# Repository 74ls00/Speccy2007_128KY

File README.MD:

# Speccy 2007 128K AY PAL SCART 2017

За основу взята единственная на тот момент полная схема 128к от Ljubitel, архив его проекта тут https://github.com/74ls00/Speccy2007_by_Ljubitel

Добавлен кодер PAL и разъём SCART.

Проект в процессе тестирования

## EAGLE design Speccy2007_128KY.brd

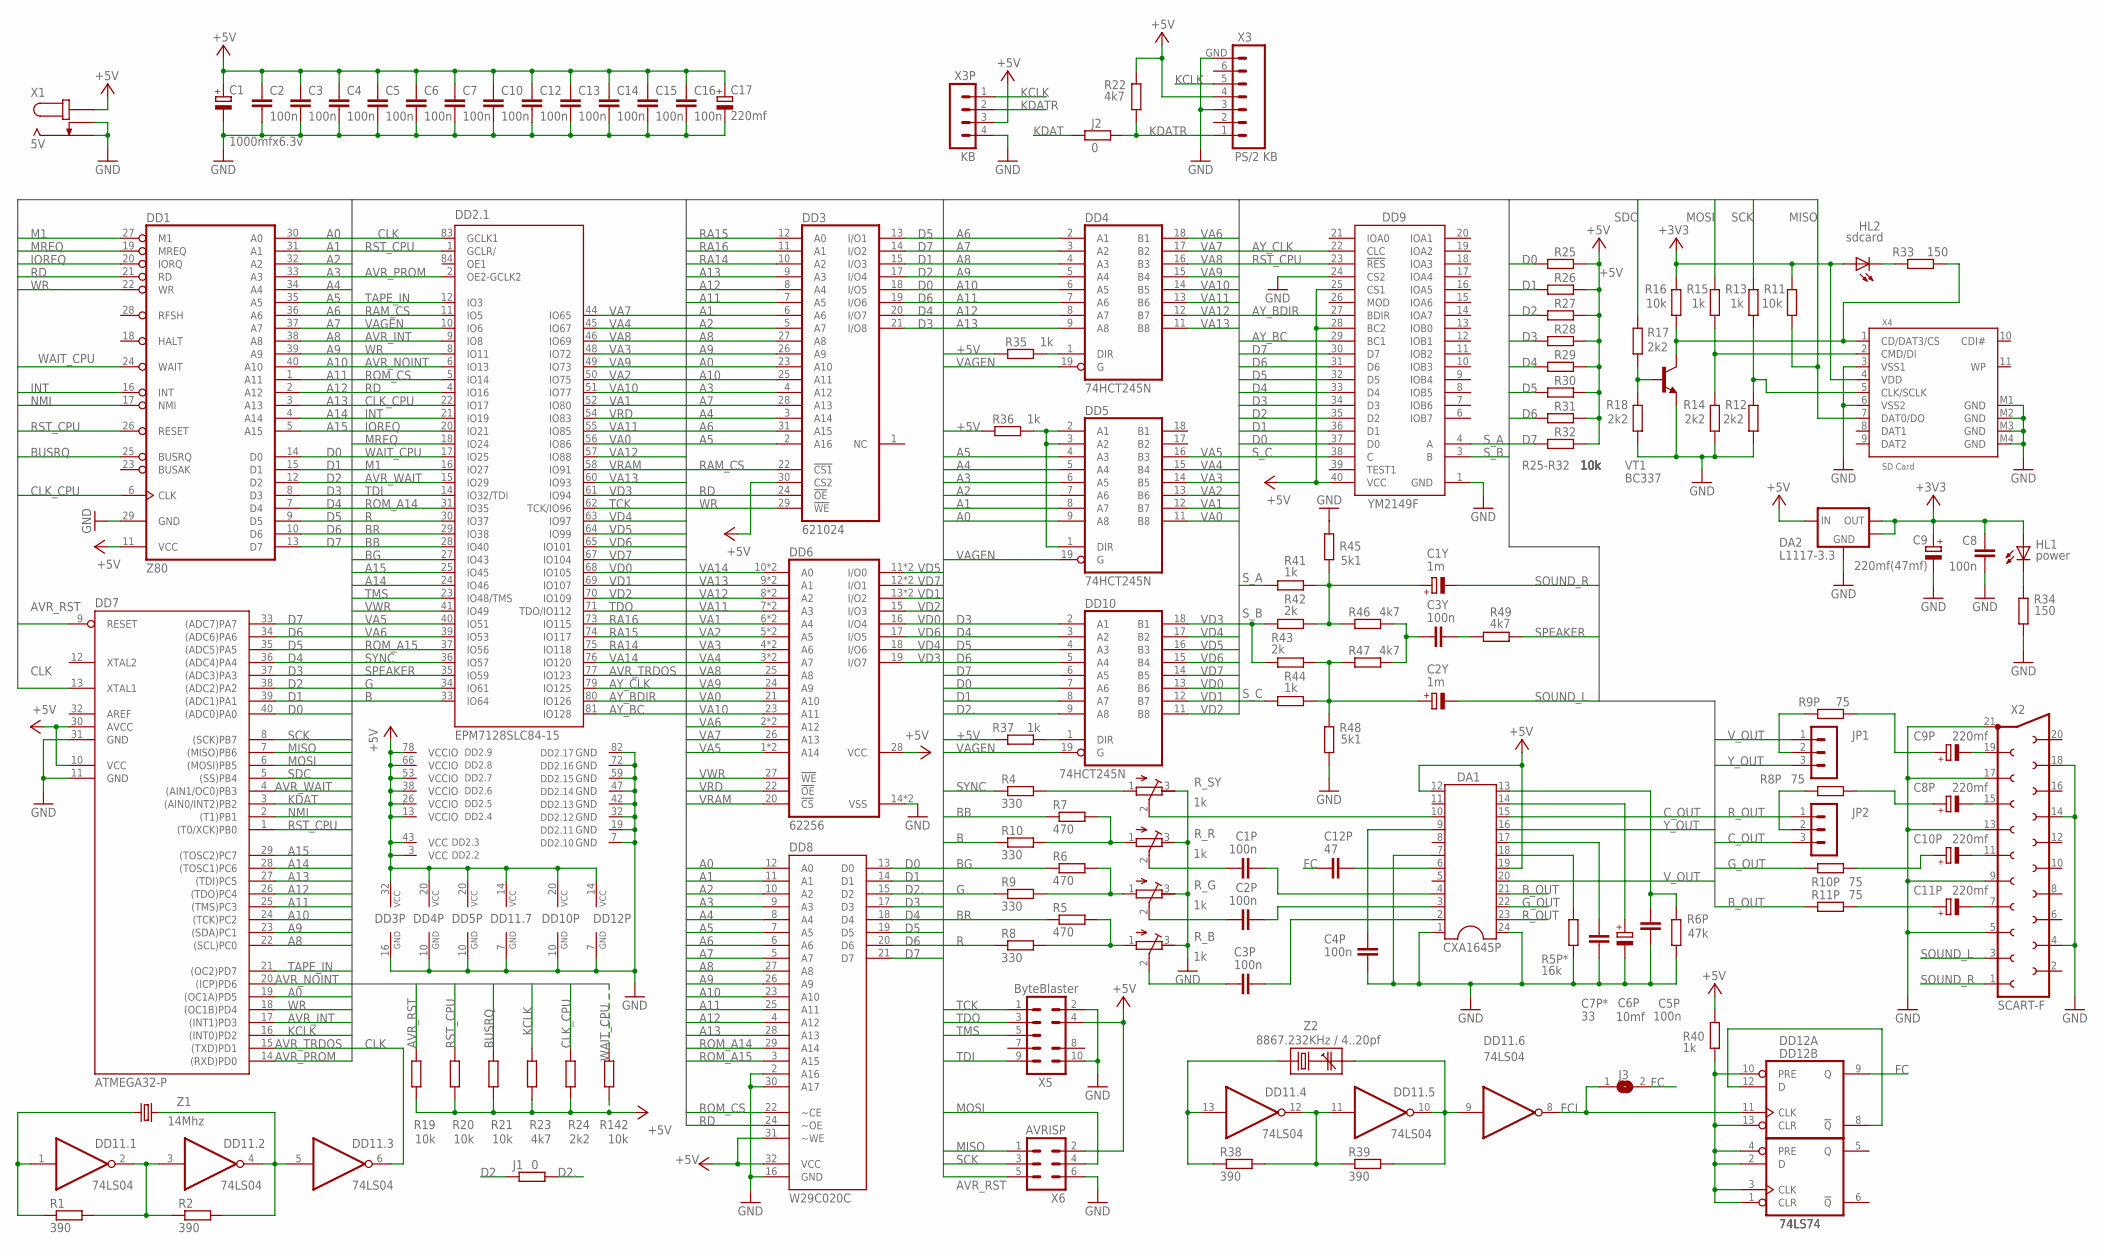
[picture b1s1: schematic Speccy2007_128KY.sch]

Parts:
C1: 1000mfx6.3v; E3,5-8
C1P, C2, C2P, C3, C3P, C3Y, C4P, C5, C7, C8, C10, C12, C13, C14, C15, C16: 100n; C0805
C1Y, C2Y: 1m; E2,5-5
C4, C5P, C6: 100n; C1206
C6P: 10mf; E2,5-5
C7P*: 33; C1206
C8P, C9P, C10P, C11P, C17: 220mf; E2,5-6
C9: 220mf(47mf); E2,5-6
C12P: 47; C0805
DA1: CXA1645P; DIL24-4
DA2: L1117-3.3; SOT-223
DD1: Z80; DIL40
DD2: EPM7128SLC84-15; PGA-84-B
DD3: 621024; DIL32
DD4, DD5, DD10: 74HCT245N; DIL20
DD6: 62256; DIL28+6
DD7: ATMEGA32-P; DIL40
DD8: W29C020C; DIL32
DD9: YM2149F; DIL40
DD11: 74LS04; DIL14
DD12: 74LS74; DIL14O
HL1: power; SML0805
HL2: sdcard; SML0805
J1: 0; M1206
J2: 0; R1206
J3: SJ
JP1, JP2: MA03-1
R1, R2, R38, R39: 390; R0805
R4, R8, R9, R10: 330; R0805
R5: 470; R0805
R5P*: 16k; M1206
R6: 470; R1206
R6P: 47k; R0805
R7: 470; 0207/10
R8P, R9P, R10P, R11P: 75; R1206
R11, R16, R20, R25, R27, R28, R29, R30, R31, R32: 10k; R0805
R12: 2k2; R1206
R13, R15, R35, R36, R37, R40, R41: 1k; R0805
R14, R17, R18: 2k2; R0805
R19, R26: 10k; M0805
R21, R142: 10k; 0207/10
R22, R47, R49: 4k7; R0805
R23, R46: 4k7; R1206
R24: 2k2; 0207/10
R33: 150; R1206
R34: 150; R0805
R42, R43: 2k; R0805
R44: 1k; R1206
R45: 5k1; R1206
R48: 5k1; R0805
R_B: 1k; RTRIM3296W
R_G: 1k; RTRIM3296W
R_R: 1k; RTRIM3296W
R_SY: 1k; RTRIM3296W
VT1: BC337; TO92-CBE
X1: 5V; POWER3.5
X2: SCART-F
X3: PS/2 KB; MINI-DIN6
X3P: KB; MA04-1
X4: SD Card; SDCMF-10915W010
X5: ByteBlaster; MA05-2
X6: AVRISP; MA03-2
Z1: 14Mhz; HC49U-H
Z2: 8867.232KHz / 4..20pf; HC49U-H

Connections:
+3V3: C8.1, C9.+, DA2.2 (OUT), DA2.4 (OUT'), HL1.A, HL2.A, R11.2, R16.2, X4.4 (VDD)
+5V: C1.+, C2.1, C3.1, C4.1, C5.1, C6.1, C7.1, C10.1, C12.1, C13.1, C14.1, C15.1, C16.1, C17.+, DA1.12, DA1.19, DA2.3 (IN), DD1.11 (VCC), DD2.3 (VCC), DD2.13 (VCCIO), DD2.26 (VCCIO), DD2.38 (VCCIO), DD2.43 (VCC), DD2.53 (VCCIO), DD2.66 (VCCIO), DD2.78 (VCCIO), DD3.30 (CS2), DD3.32 (VCC), DD4.20 (VCC), DD5.20 (VCC), DD6.28 (VCC), DD7.10 (VCC), DD7.30 (AVCC), DD8.31 (~WE), DD8.32 (VCC), DD9.25 (CS1), DD9.28 (BC2), DD9.40 (VCC), DD10.20 (VCC), DD11.14 (VCC), DD12.14 (VCC), R19.1, R20.1, R21.1, R22.2, R23.1, R24.1, R25.2, R26.2, R27.2, R28.2, R29.2, R30.2, R31.2, R32.2, R35.2, R36.2, R37.2, R40.2, R142.1, X1.P$1 (1), X3.4, X3P.3, X5.4, X6.2
A0: DD1.30 (A0), DD3.23 (A10), DD5.9 (A8), DD7.19 ((OC1A)PD5), DD8.12 (A0)
A1: DD1.31 (A1), DD3.6 (A6), DD5.8 (A7), DD8.11 (A1)
A2: DD1.32 (A2), DD3.5 (A7), DD5.7 (A6), DD8.10 (A2)
A3: DD1.33 (A3), DD3.4 (A12), DD5.6 (A5), DD8.9 (A3)
A4: DD1.34 (A4), DD3.3 (A14), DD5.5 (A4), DD8.8 (A4)
A5: DD1.35 (A5), DD3.2 (A16), DD5.4 (A3), DD8.7 (A5)
A6: DD1.36 (A6), DD3.31 (A15), DD4.2 (A1), DD8.6 (A6)
A7: DD1.37 (A7), DD3.28 (A13), DD4.3 (A2), DD8.5 (A7)
A8: DD1.38 (A8), DD3.27 (A8), DD4.4 (A3), DD7.22 ((SCL)PC0), DD8.27 (A8)
A9: DD1.39 (A9), DD3.26 (A9), DD4.5 (A4), DD7.23 ((SDA)PC1), DD8.26 (A9)
A10: DD1.40 (A10), DD3.25 (A11), DD4.6 (A5), DD7.24 ((TCK)PC2), DD8.23 (A10)
A11: DD1.1 (A11), DD3.7 (A5), DD4.7 (A6), DD7.25 ((TMS)PC3), DD8.25 (A11)
A12: DD1.2 (A12), DD3.8 (A4), DD4.8 (A7), DD7.26 ((TDO)PC4), DD8.4 (A12)
A13: DD1.3 (A13), DD3.9 (A3), DD4.9 (A8), DD7.27 ((TDI)PC5), DD8.28 (A13)
A14: DD1.4 (A14), DD2.24 (IO46), DD7.28 ((TOSC1)PC6)
A15: DD1.5 (A15), DD2.25 (IO45), DD7.29 ((TOSC2)PC7)
AVR_INT: DD2.9 (IO8), DD7.17 ((INT1)PD3)
AVR_NOINT: DD2.6 (IO13), DD7.20 ((ICP)PD6)
AVR_PROM: DD2.2 (OE2-GCLK2), DD7.14 ((RXD)PD0)
AVR_RST: DD7.9 (RESET), R19.2, X6.5
AVR_TRDOS: DD2.77 (IO123), DD7.15 ((TXD)PD1)
AVR_WAIT: DD2.15 (IO29), DD7.4 ((AIN1/OC0)PB3)
AY_BC: DD2.81 (IO128), DD9.29 (BC1)
AY_BDIR: DD2.80 (IO126), DD9.27 (BDIR)
AY_CLK: DD2.79 (IO125), DD9.22 (CLC)
B: DD2.33 (IO64), R10.1
BB: DD2.28 (IO40), R7.1
BG: DD2.27 (IO43), R6.1
BR: DD2.29 (IO38), R5.1
BUSRQ: DD1.25 (BUSRQ), R21.2
B_OUT: DA1.21, R11P.1
CDDAT3: R16.1, R33.1, VT1.C, X4.1 (CD/DAT3/CS)
CLK: DD2.83 (GCLK1), DD7.13 (XTAL1), DD11.6 (O)
CLK_CPU: DD1.6 (CLK), DD2.22 (IO17), R24.2
C_OUT: DA1.15, JP2.3
D0: DD1.14 (D0), DD3.18 (I/O5), DD7.40 ((ADC0)PA0), DD8.13 (D0), DD9.37 (D0), DD10.7 (A6), R25.1
D1: DD1.15 (D1), DD3.15 (I/O3), DD7.39 ((ADC1)PA1), DD8.14 (D1), DD9.36 (D1), DD10.8 (A7), R26.1
D2: DD1.12 (D2), DD7.38 ((ADC2)PA2), DD9.35 (D2), J1.1, R27.1
D2.: DD3.17 (I/O4), DD8.15 (D2), DD10.9 (A8), J1.2
D3: DD1.8 (D3), DD3.21 (I/O8), DD7.37 ((ADC3)PA3), DD8.17 (D3), DD9.34 (D3), DD10.2 (A1), R28.1
D4: DD1.7 (D4), DD3.20 (I/O7), DD7.36 ((ADC4)PA4), DD8.18 (D4), DD9.33 (D4), DD10.3 (A2), R29.1
D5: DD1.9 (D5), DD3.13 (I/O1), DD7.35 ((ADC5)PA5), DD8.19 (D5), DD9.32 (D5), DD10.4 (A3), R30.1
D6: DD1.10 (D6), DD3.19 (I/O6), DD7.34 ((ADC6)PA6), DD8.20 (D6), DD9.31 (D6), DD10.5 (A4), R31.1
D7: DD1.13 (D7), DD3.14 (I/O2), DD7.33 ((ADC7)PA7), DD8.21 (D7), DD9.30 (D7), DD10.6 (A5), R32.1
FC: C12P.1, DD12.9 (Q), J3.2
FCI: DD11.8 (O), DD12.11 (CLK), J3.1
G: DD2.34 (IO61), R9.1
GND: C1.-, C2.2, C3.2, C4.2, C4P.1, C5.2, C5P.1, C6.2, C6P.-, C7.2, C7P*.2, C8.2, C9.-, C10.2, C12.2, C13.2, C14.2, C15.2, C16.2, C17.-, DA1.1, DA1.7, DA1.24, DA2.1 (GND), DD1.29 (GND), DD2.7 (GND), DD2.19 (GND), DD2.32 (GND), DD2.42 (GND), DD2.47 (GND), DD2.59 (GND), DD2.72 (GND), DD2.82 (GND), DD3.16 (GND), DD4.10 (GND), DD5.10 (GND), DD6.14 (VSS), DD6.P$14 (VSS), DD7.11 (GND), DD7.31 (GND), DD8.2 (A16), DD8.16 (GND), DD8.30 (A17), DD9.1 (GND), DD9.24 (CS2), DD10.10 (GND), DD11.7 (GND), DD12.7 (GND), R5P*.1, R6P.1, R12.1, R14.1, R18.1, R34.1, R45.2, R48.2, R_B.3 (A), R_G.3 (A), R_R.3 (A), R_SY.3 (A), VT1.E, X1.P$2 (2), X1.P$3 (3), X2.4, X2.5, X2.9, X2.13, X2.14, X2.17, X2.18, X2.21, X3.3, X3.GND (7), X3P.4, X4.3 (VSS1), X4.6 (VSS2), X4.M1 (GND), X4.M2 (GND), X4.M3 (GND), X4.M4 (GND), X5.2, X5.10, X6.6
G_OUT: DA1.22, R10P.1
INT: DD1.16 (INT), DD2.21 (IO19)
IOREQ: DD1.20 (IORQ), DD2.20 (IO21)
KCLK: DD7.16 ((INT0)PD2), R23.2, X3.5, X3P.1
KDAT: DD7.3 ((AIN0/INT2)PB2), J2.1
KDATR: J2.2, R22.1, X3.1, X3P.2
M1: DD1.27 (M1), DD2.16 (IO27)
MISO: DD7.7 ((MISO)PB6), R11.1, X4.7 (DAT0/DO), X6.1
MOSI: DD7.6 ((MOSI)PB5), R15.2, X6.4
MREQ: DD1.19 (MREQ), DD2.18 (IO24)
unnamed: DD11.4 (O), DD11.5 (I), R2.2, Z1.2
unnamed: C3Y.1, R46.2, R47.2
unnamed: C3Y.2, R49.1
unnamed: C1Y.+, R41.2, R42.2, R45.1, R46.1
unnamed: DD11.2 (O), DD11.3 (I), R1.2, R2.1
unnamed: R4.2, R_SY.1 (E)
unnamed: C2Y.+, R43.2, R44.2, R47.1, R48.1
unnamed: R7.2, R10.2, R_R.1 (E)
unnamed: R6.2, R9.2, R_G.1 (E)
unnamed: R5.2, R8.2, R_B.1 (E)
unnamed: C1P.1, R_R.2 (S)
unnamed: DD11.1 (I), R1.1, Z1.1
unnamed: C2P.1, R_G.2 (S)
unnamed: C3P.1, R_B.2 (S)
unnamed: R17.1, R18.2, VT1.B
unnamed: R12.2, R13.1, X4.5 (CLK/SCLK)
unnamed: R14.2, R15.1, X4.2 (CMD/DI)
unnamed: DA1.10, R_SY.2 (S)
unnamed: DD10.1 (DIR), R37.1
unnamed: DD5.1 (DIR), DD5.2 (A1), DD5.3 (A2), R36.1
unnamed: C9P.-, X2.19
unnamed: JP1.2, R9P.1
unnamed: C4P.2, DA1.9
unnamed: C8P.-, X2.15
unnamed: JP2.2, R8P.1
unnamed: C10P.-, X2.11
unnamed: C11P.-, X2.7
unnamed: C10P.+, R10P.2
unnamed: C3P.2, DA1.2
unnamed: C11P.+, R11P.2
unnamed: DD12.8 (!Q), DD12.12 (D)
unnamed: HL1.C, R34.2
unnamed: DD12.1 (CLR), DD12.2 (D), DD12.3 (CLK), DD12.4 (PRE), DD12.10 (PRE), DD12.13 (CLR), R40.1
unnamed: HL2.C, R33.2
unnamed: DD4.1 (DIR), R35.1
unnamed: DD11.11 (I), DD11.12 (O), R38.2, R39.1
unnamed: DD11.9 (I), DD11.10 (O), R39.2, Z2.2
unnamed: DD11.13 (I), R38.1, Z2.1
unnamed: C2P.2, DA1.3
unnamed: C1P.2, DA1.4
unnamed: C9P.+, R9P.2
unnamed: DA1.18, R5P*.2
unnamed: C5P.2, DA1.13, R6P.2
unnamed: C6P.+, DA1.14
unnamed: C8P.+, R8P.2
unnamed: C12P.2, DA1.6
unnamed: C7P*.1, DA1.17
NMI: DD1.17 (NMI), DD7.2 ((T1)PB1)
R: DD2.30 (IO37), R8.1
RA14: DD2.75 (IO118), DD3.10 (A2)
RA15: DD2.74 (IO117), DD3.12 (A0)
RA16: DD2.73 (IO115), DD3.11 (A1)
RAM_CS: DD2.11 (IO5), DD3.22 (!CS1)
RD: DD1.21 (RD), DD2.4 (IO16), DD3.24 (!OE), DD8.24 (~OE)
ROM_A14: DD2.31 (IO35), DD8.29 (A14)
ROM_A15: DD2.37 (IO56), DD8.3 (A15)
ROM_CS: DD2.5 (IO14), DD8.22 (~CE)
RST_CPU: DD1.26 (RESET), DD2.1 (GCLR/), DD7.1 ((T0/XCK)PB0), DD9.23 (!RES), R20.2
R_OUT: DA1.23, JP2.1
SCK: DD7.8 ((SCK)PB7), R13.2, X6.3
SDC: DD7.5 ((SS)PB4), R17.2
SOUND_L: C2Y.-, X2.3
SOUND_R: C1Y.-, X2.1
SPEAKER: DD2.35 (IO59), R49.2
SYNC: DD2.36 (IO57), R4.1
S_A: DD9.4 (A), R41.1
S_B: DD9.3 (B), R42.1, R43.1
S_C: DD9.38 (C), R44.1
TAPE_IN: DD2.12 (IO3), DD7.21 ((OC2)PD7)
TCK: DD2.62 (TCK/IO96), X5.1
TDI: DD2.14 (IO32/TDI), X5.9
TDO: DD2.71 (TDO/IO112), X5.3
TMS: DD2.23 (IO48/TMS), X5.5
VA0: DD2.56 (IO86), DD5.11 (B8), DD6.21 (A10)
VA1: DD2.52 (IO80), DD5.12 (B7), DD6.6 (A4), DD6.P$6 (A4)
VA2: DD2.50 (IO75), DD5.13 (B6), DD6.5 (A5), DD6.P$5 (A5)
VA3: DD2.48 (IO72), DD5.14 (B5), DD6.4 (A6), DD6.P$4 (A6)
VA4: DD2.45 (IO67), DD5.15 (B4), DD6.3 (A7), DD6.P$3 (A7)
VA5: DD2.40 (IO51), DD5.16 (B3), DD6.1 (A14), DD6.P$1 (A14)
VA6: DD2.39 (IO53), DD4.18 (B1), DD6.2 (A12), DD6.P$2 (A12)
VA7: DD2.44 (IO65), DD4.17 (B2), DD6.26 (A13)
VA8: DD2.46 (IO69), DD4.16 (B3), DD6.25 (A8)
VA9: DD2.49 (IO73), DD4.15 (B4), DD6.24 (A9)
VA10: DD2.51 (IO77), DD4.14 (B5), DD6.23 (A11)
VA11: DD2.55 (IO85), DD4.13 (B6), DD6.7 (A3), DD6.P$7 (A3)
VA12: DD2.57 (IO88), DD4.12 (B7), DD6.8 (A2), DD6.P$8 (A2)
VA13: DD2.60 (IO93), DD4.11 (B8), DD6.9 (A1), DD6.P$9 (A1)
VA14: DD2.76 (IO120), DD6.10 (A0), DD6.P$10 (A0)
VAGEN: DD2.10 (IO6), DD4.19 (G), DD5.19 (G), DD10.19 (G)
VD0: DD2.68 (IO105), DD6.16 (I/O4), DD10.13 (B6)
VD1: DD2.69 (IO107), DD6.13 (I/O2), DD6.P$13 (I/O2), DD10.12 (B7)
VD2: DD2.70 (IO109), DD6.15 (I/O3), DD10.11 (B8)
VD3: DD2.61 (IO94), DD6.19 (I/O7), DD10.18 (B1)
VD4: DD2.63 (IO97), DD6.18 (I/O6), DD10.17 (B2)
VD5: DD2.64 (IO99), DD6.11 (I/O0), DD6.P$11 (I/O0), DD10.16 (B3)
VD6: DD2.65 (IO101), DD6.17 (I/O5), DD10.15 (B4)
VD7: DD2.67 (IO104), DD6.12 (I/O1), DD6.P$12 (I/O1), DD10.14 (B5)
VRAM: DD2.58 (IO91), DD6.20 (!CS)
VRD: DD2.54 (IO83), DD6.22 (!OE)
VWR: DD2.41 (IO49), DD6.27 (!WE)
V_OUT: DA1.20, JP1.1
WAIT_CPU: DD1.24 (WAIT), DD2.17 (IO25), R142.2
WR: DD1.22 (WR), DD2.8 (IO11), DD3.29 (!WE), DD7.18 ((OC1B)PD4)
Y_OUT: DA1.16, JP1.3

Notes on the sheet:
R25-R32

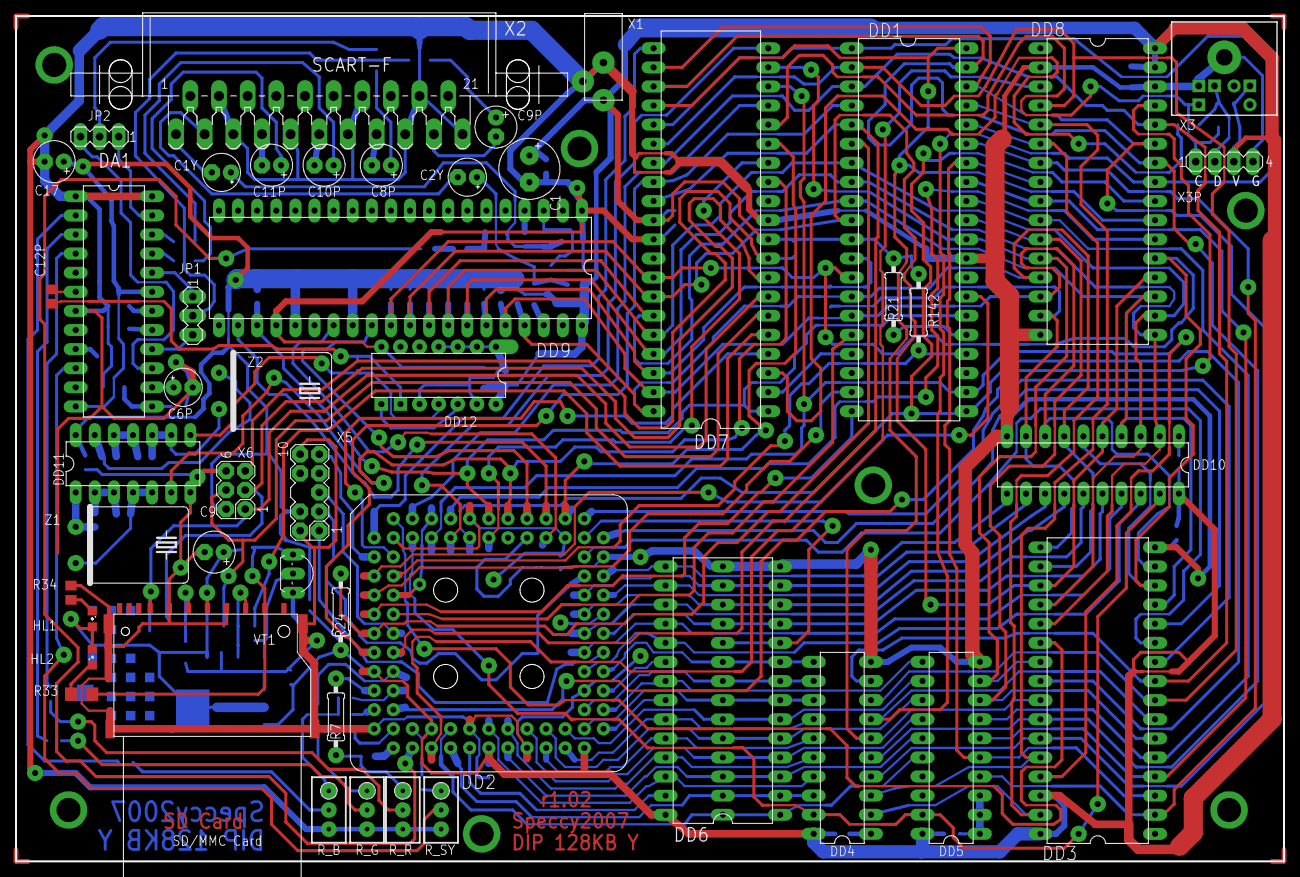
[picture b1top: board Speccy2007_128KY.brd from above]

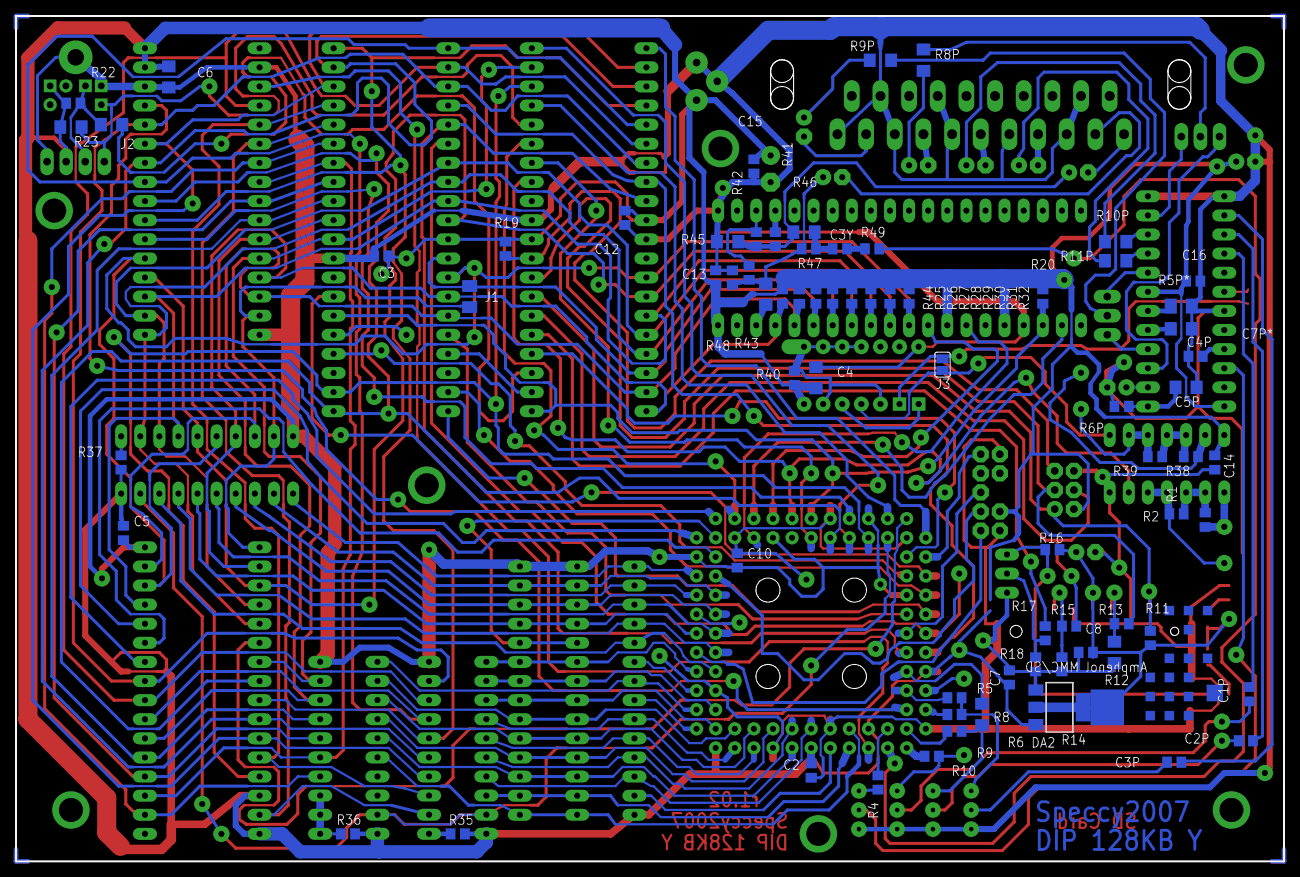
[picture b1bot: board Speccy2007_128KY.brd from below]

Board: 2 copper layers, 168.6 x 112.4 mm, 121 parts (73 on the bottom side), 164 nets.

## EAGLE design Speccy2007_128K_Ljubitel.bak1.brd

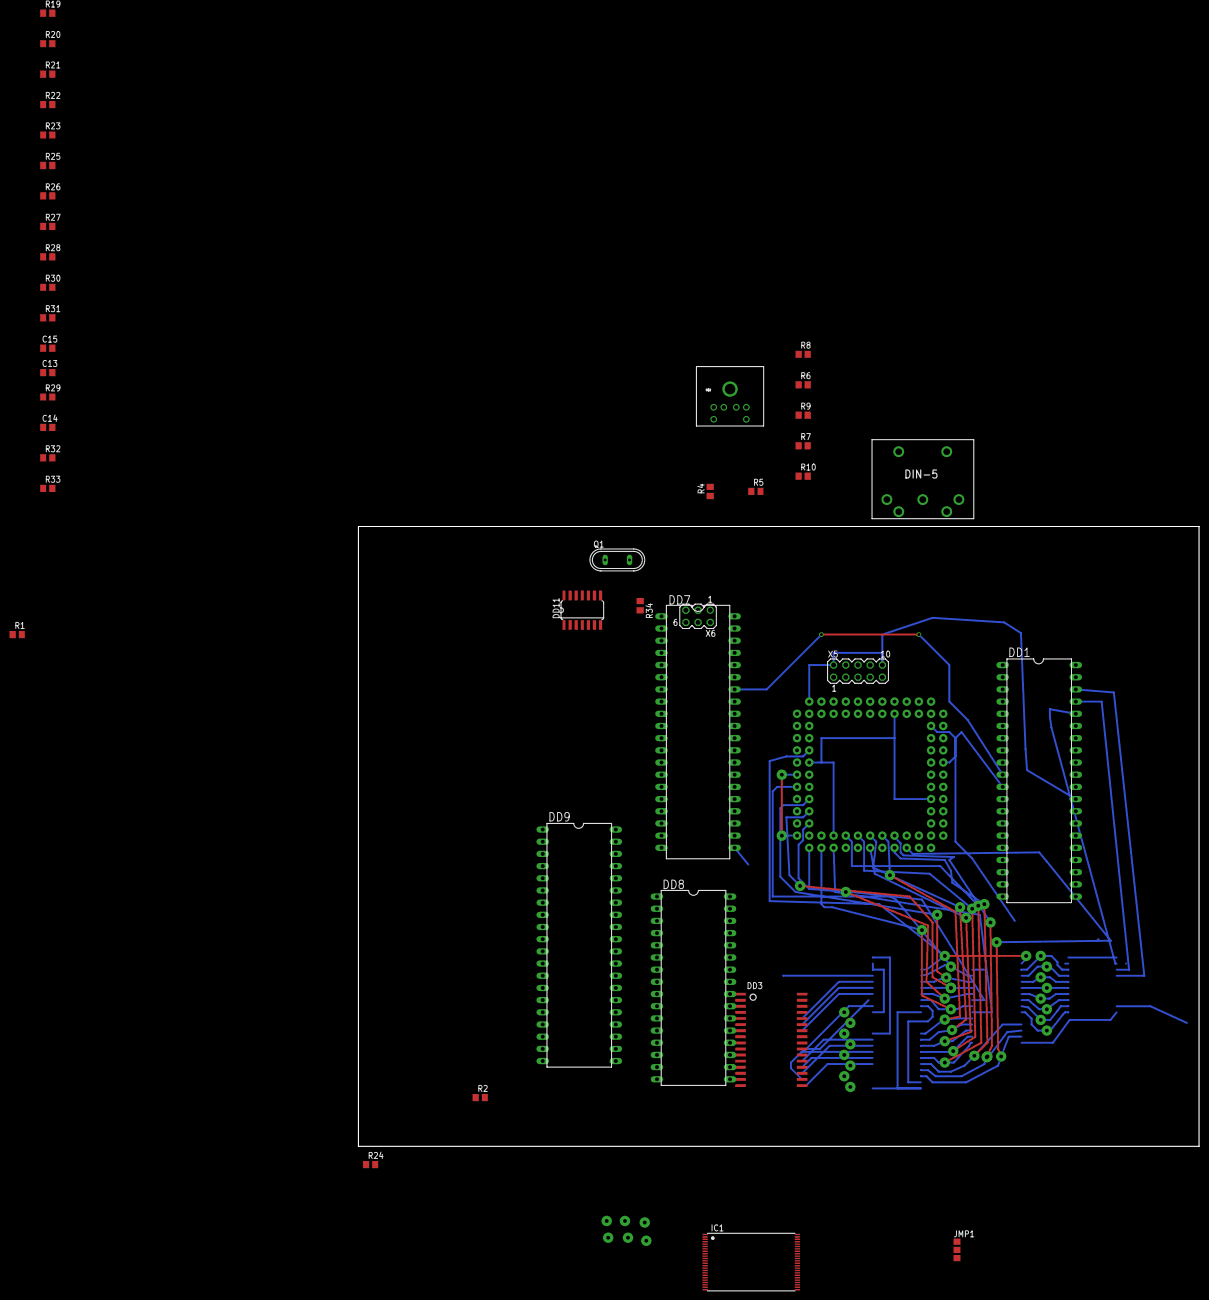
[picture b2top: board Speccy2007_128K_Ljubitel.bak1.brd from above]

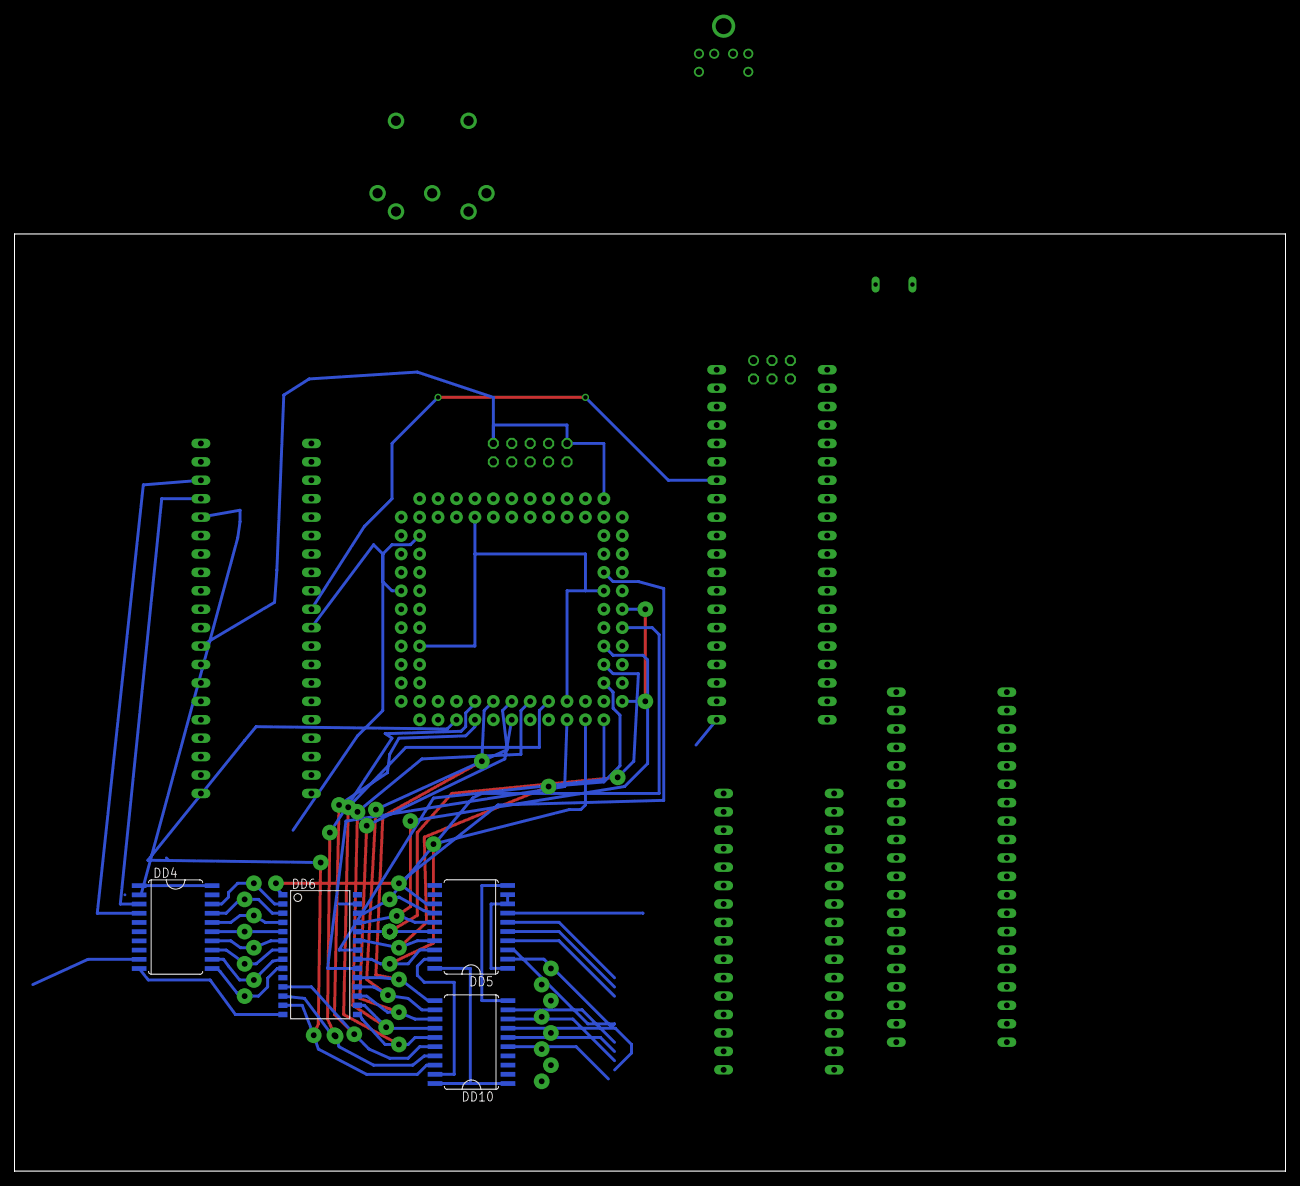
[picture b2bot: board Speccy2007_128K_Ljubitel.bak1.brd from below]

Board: 2 copper layers, 175.2 x 129.2 mm, 46 parts (4 on the bottom side), 113 nets.

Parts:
C13, C14: 1m; C0805
C15: 0.1; C0805
DD1: Z80; DIL40
DD2: EPM7128-J84; PGA-84
DD3: 621024; SOP32L
DD4, DD5, DD10: 74HCT245DW; SO20W
DD6: 62256; SO28L
DD7: MEGA16-P; DIL40
DD8: W29C020C; DIL32
DD9: YM2149F; DIL40
DD11: 74HC00D; SO14
IC1: SST39LF800A; TSOP48
JMP1: A0R-JMP
Q1: 14Mhz; QS
R1, R22, R23, R30, R31, R33: 4k7; R0805
R2, R24: 2k2; R0805
R4, R8, R9, R10: 330; R0805
R5, R6, R7: 470; R0805
R19, R20, R21: 10k; R0805
R25, R28: 1k; R0805
R26, R27: 2k; R0805
R29, R32: 5k1; R0805
R34: 360; R0805
U$1: MIDI_CONN_FEMALE_SUPPORT; DIN_5_FEMALE_SUPPORT
U$2: MINI-DIN6PTH; MINI-DIN6
X5: ByteBlaster; MA05-2
X6: AVRISP; MA03-2

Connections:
+5V: DD1.11, DD2.3, DD2.13, DD2.26, DD2.38, DD2.43, DD2.53, DD2.66, DD2.78, DD3.32, DD4.1, DD4.20, DD5.1, DD5.8, DD5.9, DD5.20, DD6.28, DD7.10, DD7.30, DD8.31, DD8.32, DD9.25, DD9.28, DD9.40, DD10.1, DD10.20, DD11.14, JMP1.1, R19.1, R20.1, R21.1, R22.1, R23.1, R24.1, X5.4, X6.2
A: DD9.4, R25.1
A0: DD1.30, DD3.23, DD5.2, DD7.19, DD8.12
A1: DD1.31, DD3.25, DD5.3, DD8.11
A2: DD1.32, DD3.26, DD5.4, DD8.10
A3: DD1.33, DD3.27, DD5.5, DD8.9
A4: DD1.34, DD3.28, DD5.6, DD8.8
A5: DD1.35, DD3.4, DD5.7, DD8.7
A6: DD1.36, DD3.12, DD4.2, DD8.6
A7: DD1.37, DD3.11, DD4.3, DD8.5
A8: DD1.38, DD3.10, DD4.4, DD7.22, DD8.27
A9: DD1.39, DD3.9, DD4.5, DD7.23, DD8.26
A10: DD1.40, DD3.8, DD4.6, DD7.24, DD8.23
A11: DD1.1, DD3.7, DD4.7, DD7.25, DD8.25
A12: DD1.2, DD3.6, DD4.8, DD7.26, DD8.4
A13: DD1.3, DD3.5, DD4.9, DD7.27, DD8.28
A14: DD1.4, DD2.24, DD7.28
A15: DD1.5, DD2.25, DD7.29
AVR_INT: DD2.9, DD7.17
AVR_NOINT: DD2.6, DD7.20
AVR_PROM: DD2.2, DD7.14
AVR_RST: DD7.9, R19.2, X6.5
AVR_TRDOS: DD2.77, DD7.15
AVR_WAIT: DD2.15, DD7.4
AY_BC: DD2.81, DD9.29
AY_BDIR: DD2.80, DD9.27
AY_CLK: DD2.79, DD9.22
B: DD2.33, DD9.3, R10.1, R26.1, R27.1
BB: DD2.28, R7.1
BG: DD2.27, R6.1
BR: DD2.29, R5.1
BUSRQ: DD1.25, R21.2
C: DD9.38, R28.1
CLK: DD2.83, DD7.13, DD11.8
CLK_CPU: DD1.6, DD2.22, R24.2
D0: DD1.14, DD3.13, DD7.40, DD8.13, DD9.37, DD10.4
D1: DD1.15, DD3.14, DD7.39, DD8.14, DD9.36, DD10.3
D2: DD1.12, DD3.15, DD7.38, DD8.15, DD9.35, DD10.2
D3: DD1.8, DD3.17, DD7.37, DD8.17, DD9.34, DD10.5
D4: DD1.7, DD3.20, DD7.36, DD8.18, DD9.33, DD10.6
D5: DD1.9, DD3.18, DD7.35, DD8.19, DD9.32, DD10.7
D6: DD1.10, DD3.19, DD7.34, DD8.20, DD9.31, DD10.8
D7: DD1.13, DD3.21, DD7.33, DD8.21, DD9.30, DD10.9
G: DD2.34, R9.1
GND: DD1.29, DD2.7, DD2.19, DD2.32, DD2.42, DD2.47, DD2.59, DD2.72, DD2.82, DD3.16, DD4.10, DD5.10, DD6.14, DD7.11, DD7.31, DD8.2, DD8.16, DD8.30, DD9.1, DD9.24, DD10.10, DD11.7, IC1.27, IC1.46, R2.1, R29.2, R32.2, X5.2, X5.10, X6.6
INT: DD1.16, DD2.21
IOREQ: DD1.20, DD2.20
KCLK: DD7.16, R23.2
KDAT: DD7.3, R22.2
M1: DD1.27, DD2.16
MISO: DD7.7, X6.1
MOSI: DD7.6, X6.4
MREQ: DD1.19, DD2.18
unnamed: DD11.1, DD11.2, Q1.2, R34.1
unnamed: C15.1, R30.2, R31.2
unnamed: C15.2, R33.1
unnamed: C13.1, R25.2, R26.2, R29.1, R30.1
unnamed: DD11.3, DD11.4, DD11.5, R34.2
unnamed: C14.1, R27.2, R28.2, R31.1, R32.1
unnamed: R5.2, R8.2
unnamed: R6.2, R9.2
unnamed: R7.2, R10.2
unnamed: DD11.6, DD11.9, DD11.10, DD11.12, DD11.13, Q1.1
unnamed: DD3.30, JMP1.2
NMI: DD1.17, DD7.2
R: DD2.30, R8.1
RAM_A14: DD2.75, DD3.3
RAM_A15: DD2.74, DD3.31
RAM_A16: DD2.73, DD3.2
RAM_CS: DD2.11, DD3.22
RD: DD1.21, DD2.4, DD3.24, DD8.24
ROM_A14: DD2.31, DD8.29
ROM_A15: DD2.37, DD8.3
ROM_CS: DD2.5, DD8.22
RST_CPU: DD1.26, DD2.1, DD7.1, DD9.23, R20.2
SCK: DD7.8, X6.3
SOUND_L: C14.2, R1.1, R2.2
SPEAKER: DD2.35, R1.2, R33.2
SYNC: DD2.36, R4.1
TAPE_IN: DD2.12, DD7.21
TCK: DD2.62, X5.1
TDI: DD2.14, X5.9
TDO: DD2.71, X5.3
TMS: DD2.23, X5.5
VA0: DD2.56, DD5.18, DD6.21
VA1: DD2.52, DD5.17, DD6.23
VA2: DD2.50, DD5.16, DD6.24
VA3: DD2.48, DD5.15, DD6.25
VA4: DD2.45, DD5.14, DD6.26
VA5: DD2.40, DD5.13, DD6.1
VA6: DD2.39, DD4.18, DD6.2
VA7: DD2.44, DD4.17, DD6.3
VA8: DD2.46, DD4.16, DD6.4
VA9: DD2.49, DD4.15, DD6.5
VA10: DD2.51, DD4.14, DD6.6
VA11: DD2.55, DD4.13, DD6.7
VA12: DD2.57, DD4.12, DD6.8
VA13: DD2.60, DD4.11, DD6.9
VA14: DD2.76, DD6.10
VAGEN: DD2.10, DD4.19, DD5.19, DD10.19
VD0: DD2.68, DD6.11, DD10.16
VD1: DD2.69, DD6.12, DD10.17
VD2: DD2.70, DD6.13, DD10.18
VD3: DD2.61, DD6.15, DD10.15
VD4: DD2.63, DD6.16, DD10.14
VD5: DD2.64, DD6.17, DD10.13
VD6: DD2.65, DD6.18, DD10.12
VD7: DD2.67, DD6.19, DD10.11
VRAM: DD2.58, DD6.20
VRD: DD2.54, DD6.22
VWR: DD2.41, DD6.27
WAIT_CPU: DD1.24, DD2.17
WR: DD1.22, DD2.8, DD3.29, DD7.18

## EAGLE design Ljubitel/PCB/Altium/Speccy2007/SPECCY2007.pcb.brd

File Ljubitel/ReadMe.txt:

Проект Speccy2007 128К от Ljubitel

http://zx-pk.ru/threads/11890-speccy2007-128k-odnoplatnyj-variant.html?p=282058&viewfull=1#post282058

Судя по последующим сообщениям сборка рабочая, но у автора получились бракованые платы и он соединял проводами.

Выкладываю как есть может кому пригодится.

Добавлен только Speccy2007_128K_Ljubitel.lay6 в tmp для оценки размеров платы

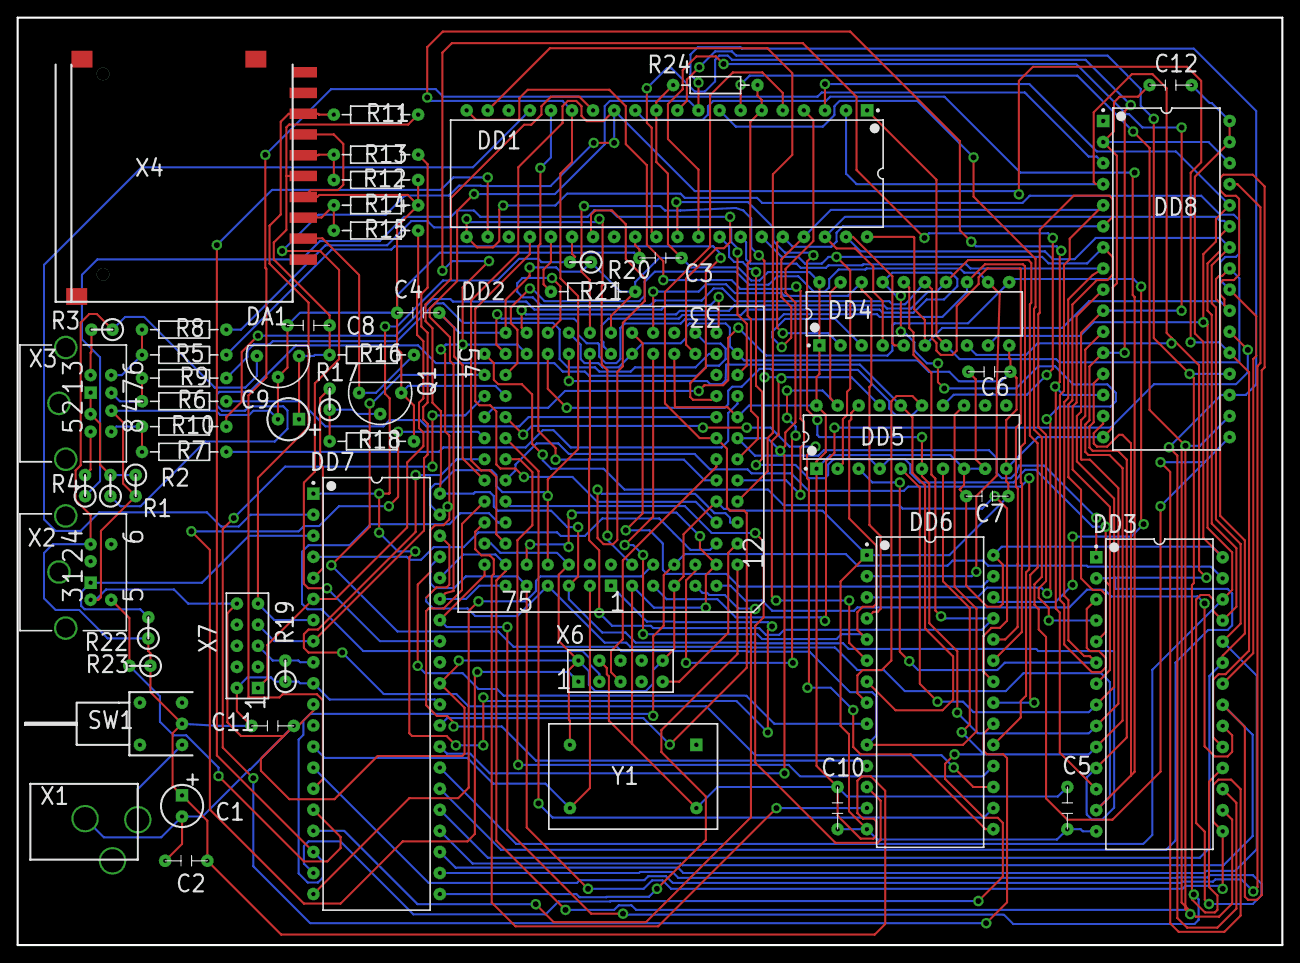
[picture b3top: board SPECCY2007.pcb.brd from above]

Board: 2 copper layers, 152.4 x 111.8 mm, 54 parts (0 on the bottom side), 103 nets.

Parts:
C1: 47,0; CAPPOL_2.54_1PRIMARY
C2, C3, C4, C5, C6, C7, C8, C10, C11, C12: 0,1; CAP_5.08-7.8X3.2_1PRIMARY
C9: 47,0; CAPPOL_2.54_2PRIMARY
DA1: LP2950; TO92_1PRIMARY
DD1: Z80A; DIP-40_1PRIMARY
DD2: EPM7128S/PLCC; PLCC84-SOCKET+ALTERAMAX700S_1PRIMARY
DD3, DD6: CY62256; DIP-28W_1PRIMARY
DD4: 74HCT245; DIP-20_1PRIMARY
DD5: 74HCT245; DIP-20_2PRIMARY
DD7: ATMEGA16; DIP-40_2PRIMARY
DD8: AT29C020; DIP-32/D41.2_1PRIMARY
Q1: BC557; TO92_2PRIMARY
R1, R22, R23: 4K7; RES-2.54_1PRIMARY
R2, R17: 2K2; RES-2.54_1PRIMARY
R3: 100; RES-2.54_1PRIMARY
R4: 330; RES-2.54_1PRIMARY
R5, R6, R7: 470; RES_10.16_1PRIMARY
R8, R9, R10: 330; RES_10.16_1PRIMARY
R11, R16, R21: 10K; RES_10.16_1PRIMARY
R12, R14, R18, R24: 2K2; RES_10.16_1PRIMARY
R13, R15: 1K; RES_10.16_1PRIMARY
R19, R20: 10K; RES-2.54_1PRIMARY
SW1: SW_T_SPDT; SW_T_SPDT_1PRIMARY
X1: X3; CONN_JACK_PWR_1PRIMARY
X2: X6; MINI-DIN6_1PRIMARY
X3: X8; MINI-DIN8_1PRIMARY
X4: X9; SD_CARD_SOCKET_1PRIMARY
X6, X7: X10; DOUBLE_ROW_PIN_STRIP_5_WAY_1PRIMARY
Y1: 14MHz; OSC14_1PRIMARY

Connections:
A0: DD1.30, DD3.10, DD5.7, DD7.19, DD8.12
A1: DD1.31, DD3.9, DD5.6, DD8.11
A2: DD1.32, DD3.8, DD5.5, DD8.10
A3: DD1.33, DD3.7, DD5.4, DD8.9
A4: DD1.34, DD3.6, DD5.3, DD8.8
A5: DD1.35, DD3.5, DD5.2, DD8.7
A6: DD1.36, DD3.4, DD4.2, DD8.6
A7: DD1.37, DD3.3, DD4.3, DD8.5
A8: DD1.38, DD3.25, DD4.4, DD7.22, DD8.27
A9: DD1.39, DD3.24, DD4.5, DD7.23, DD8.26
A10: DD1.40, DD3.21, DD4.6, DD7.24, DD8.23
A11: DD1.1, DD3.23, DD4.7, DD7.25, DD8.25
A12: DD1.2, DD3.2, DD4.8, DD7.26, DD8.4
A13: DD1.3, DD3.26, DD4.9, DD7.27, DD8.28
A14: DD1.4, DD2.24, DD3.1, DD7.28
A15: DD1.5, DD2.25, DD7.29
AVR_INT: DD2.9, DD7.17
AVR_NOINT: DD2.6, DD7.20
AVR_RST: DD7.9, R19.2, X7.5
AVR_WAIT: DD2.15, DD7.4
B: DD2.33, R10.1
BB: DD2.28, R7.1
BG: DD2.27, R6.1
BR: DD2.29, R5.1
BUSRQ: DD1.25, R21.2
CLK: DD2.83, DD7.13, Y1.3
CLK_CPU: DD1.6, DD2.22, R24.2
D0: DD1.14, DD2.81, DD3.11, DD7.40, DD8.13
D1: DD1.15, DD2.80, DD3.12, DD7.39, DD8.14
D2: DD1.12, DD2.79, DD3.13, DD7.38, DD8.15
D3: DD1.8, DD2.77, DD3.15, DD7.37, DD8.17
D4: DD1.7, DD2.76, DD3.16, DD7.36, DD8.18
D5: DD1.9, DD2.75, DD3.17, DD7.35, DD8.19
D6: DD1.10, DD2.74, DD3.18, DD7.34, DD8.20
D7: DD1.13, DD2.73, DD3.19, DD7.33, DD8.21
G: DD2.34, R9.1
GND: C1.1, C2.2, C3.2, C4.2, C5.2, C6.2, C7.2, C8.2, C9.1, C10.2, C11.2, C12.2, DA1.2, DD1.29, DD2.7, DD2.19, DD2.32, DD2.42, DD2.47, DD2.59, DD2.72, DD2.82, DD3.14, DD4.10, DD5.10, DD6.1, DD6.14, DD7.11, DD7.31, DD8.2, DD8.16, DD8.30, Q1.1, R2.2, R12.2, R14.2, R18.1, X1.1, X2.3, X3.4, X4.3, X4.6, X6.2, X6.10, X7.10, Y1.2
INT: DD1.16, DD2.21
IOREQ: DD1.20, DD2.20
KCLK: DD7.16, R23.2, X2.5
KDAT: DD7.3, R22.2, X2.1
M1: DD1.27, DD2.16
MISO: DD7.7, R11.2, X4.7, X7.9
MOSI: DD7.6, R15.1, X7.1
MREQ: DD1.19, DD2.18
NETC8_1: C8.1, C9.2, DA1.1, R11.1, R16.2, X4.4
NETQ1_2: Q1.2, R17.1, R18.2
NETQ1_3: Q1.3, R16.1, X4.1
NETR1_2: R1.2, R2.1, X3.1, X3.2
NETR3_2: R3.2, X3.3
NETR4_2: R4.2, X3.5
NETR5_2: R5.2, R8.2, X3.6
NETR6_2: R6.2, R9.2, X3.7
NETR7_2: R7.2, R10.2, X3.8
NETR12_1: R12.1, R13.2, X4.5
NETR14_1: R14.1, R15.2, X4.2
NETSW1_1: SW1.1, X1.3
NMI: DD1.17, DD7.2
R: DD2.30, R8.1
RAM: DD2.11, DD3.20
RD: DD1.21, DD2.4, DD3.22, DD8.24
ROM: DD2.5, DD8.22
ROM0: DD7.14, DD8.29
ROM1: DD7.15, DD8.3
RST_CPU: DD1.26, DD2.1, DD7.1, R20.2
SCK: DD7.8, R13.1, X7.7
SDC: DD7.5, R17.2
SOUND: DD2.35, R1.1
SYNC: DD2.36, R4.1
TAPE_IN: DD2.12, DD7.21
TCK: DD2.62, X6.1
TDI: DD2.14, X6.9
TDO: DD2.71, X6.3
TMS: DD2.23, X6.5
VA0: DD2.56, DD5.13, DD6.10
VA1: DD2.52, DD5.14, DD6.9
VA2: DD2.50, DD5.15, DD6.8
VA3: DD2.48, DD5.16, DD6.7
VA4: DD2.45, DD5.17, DD6.6
VA5: DD2.40, DD5.18, DD6.5
VA6: DD2.39, DD4.18, DD6.4
VA7: DD2.44, DD4.17, DD6.3
VA8: DD2.46, DD4.16, DD6.25
VA9: DD2.49, DD4.15, DD6.24
VA10: DD2.51, DD4.14, DD6.21
VA11: DD2.55, DD4.13, DD6.23
VA12: DD2.57, DD4.12, DD6.2
VA13: DD2.60, DD4.11, DD6.26
VAGEN: DD2.10, DD4.19, DD5.19
VCC: C1.2, C2.1, C3.1, C4.1, C5.1, C6.1, C7.1, C10.1, C11.1, C12.1, DA1.3, DD1.11, DD2.3, DD2.13, DD2.26, DD2.38, DD2.43, DD2.53, DD2.66, DD2.78, DD3.28, DD4.1, DD4.20, DD5.1, DD5.8, DD5.9, DD5.20, DD6.28, DD7.10, DD7.30, DD8.31, DD8.32, R3.1, R19.1, R20.1, R21.1, R22.1, R23.1, R24.1, SW1.2, X2.4, X6.4, X7.2, Y1.4
VD0: DD2.68, DD6.11
VD1: DD2.69, DD6.12
VD2: DD2.70, DD6.13
VD3: DD2.61, DD6.15
VD4: DD2.63, DD6.16
VD5: DD2.64, DD6.17
VD6: DD2.65, DD6.18
VD7: DD2.67, DD6.19
VRAM: DD2.58, DD6.20
VRD: DD2.54, DD6.22
VWR: DD2.41, DD6.27
WAIT_CPU: DD1.24, DD2.17
WR: DD1.22, DD2.8, DD3.27, DD7.18

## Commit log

2017-02-01 lbr bak
2017-02-11 head
2017-10-19 fix pal 1
2017-10-26 clear
2017-10-26 +pic rm
2017-11-01 .clear
2019-12-20 2019.0
2019-12-30 power

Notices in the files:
parts and their libraries:
SparkFun-Connectors: Licensing: Creative Commons ShareAlike 4.0 International - https://creativecommons.org/licenses/by-sa/4.0
